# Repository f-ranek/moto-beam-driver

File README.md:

# Cel projektu

Celem projektu było zbudowanie prostego urządzenia, które wyłączy światła mijania, gdy nie są potrzebne.
Dedykowane dla motocykla Suzuki V-Strom 650, roczniki od 2017 wzwyż.

## Od strony użytkownika

Zacznijmy od tego, że podchodzę do motocykla, włączam stacyjkę. Normalnie światła już świecą, ale po co. Póki co mam odcięty zapłon na _kill-switch_, a bieg na luzie. Włączam _kill-switch_, odpalam moto, ale ja przecież jeszcze nigdzie nie jadę - kask trzeba ubrać, wsiąść, stopkę złożyć. I gdy już to wszystko jest zrobione, włączam bieg (magia, ta dam), światła się zapalają, a ja odjeżdżam. Niekoniecznie w stronę słońca, bo czasem razi, ale na pewno gdzieś daleko.

Dojeżdżając do skrzyżowania, wrzucam luz, ale wtedy światła już nie gasną. No chyba, że dojechałem do przejazdu kolejowego, i wiem, że chwilę postoję. Gaszę wtedy silnik, a po chwili światła automatycznie gasną. Zapalą się znów, gdy będzie włączony silnik i bieg.
A gdyby mi po drodze przez przypadek zgasł silnik, to światła zgasną również na czas kręcenia rozrusznikiem.

Dodatkowo, mam do dyspozycji przycisk, który zmienia stan świateł na przeciwne (włączone-wyłączone). Przykładowo, gdy chcę sobie poświecić. Albo na czas jazdy w _offie_ wyłączyć światła.

Funkcjonalność, której niestety nie zweryfikowałem w praktyce to utrzymywanie napięcia na żarówce na poziomie około 13,2 V napięcia skutecznego pomimo wahań napięcia w instalacji motocykla. Celem tego zabiegu jest przedłużenie żywotniści żarówki świateł mijania. Niestety, jak napisałem, z braku czasu nie sprawdziłem realnego zasięgu świateł przy obniżonym napięciu zasilania vs pełne napięcie z alternatora. Niemniej jednak obecnie zbudowany prototyp został wyposażony w czujnik zmierzchowy, który można włączyć w obwód przez aktualizację oprogramowania, i w przypadku wykrycia jazdy po zmierzchu, zasilić żarówkę pełną mocą. 

## Dioda

Dioda generalnie odzwierciedla stan świateł, tzn. powinna być włączona, gdy światła są włączone, oraz wyłączona, gdy są wyłączone.
Dodatkowo, po włączeniu stacyjki, świeci się przez trzy sekundy, nawet jeżeli światła są wyłączone.

Jeżeli dioda miga krótkimi, pojedynczymi „mrugnięciami”, bądź w podobny sposób gaśnie, to znaczy, że żarówka albo bezpiecznik są przepalone.

Po zgaszeniu silnika, ale zanim światła zgasną, jest jeszcze 5-cio sekundowy okres, w trakcie którego dioda świeci przez 0,8 sek, a następnie gaśnie na 0,2 sek.

Natomiast stan, gdy żarówka właśnie się zapala jest sygnalizowany świeceniem przez pół sekundy, i podobnie kolejne pół gaśnie. 

## Przycisk

Przycisk generalnie zmienia stan układu na przeciwny. Od tej reguły jest jeden wyjątek - przyciśnięcie go, gdy światła mają za chwilę zgasnąć (po zgaszeniu silnika) powoduje, że pozostaną włączone. Dodatkowo, przytrzymanie przycisku na dłużej niż sekundę zawsze gasi światła.

Powyższy diagram wydaje się być przerażająco skomplikowany, ale tak naprawdę realizuje logikę pozwalającą przełączać i automatycznie gasić światła.

Po załączeniu stacyjki aplikacja jest w stanie początkowym - 0.
Naciskając przycisk przy zgaszonym silniku wymuszamy włączenie i pozostawienie świateł włączonych - stany 6 i 7.
Naciskając przycisk przy włączonym silniku zapalamy światła, jednocześnie pozwalając im zgasnąć, gdy silnik zostanie zgaszony - stany 2 i 3.
Przytrzymując przycisk wymuszamy zgaszenie świateł - stan 1.

W stanie 2 światła się rozjaśniają, by automatycznie przejść do stanu 3, w którym świecą, ale mogą zgasnąć (stan 5) po pewnym czasie od zgaszenia silnika (stan 4 - przejściowy).

Podobnie ze stanu 5 po odpaleniu silnika światła się zapalą - stany 2 i 3.

Stany 6 i 7 to wymuszone włączenie świateł - nie zgasną po zgaszeniu silnika, a tylko na czas kręcenia rozrusznikiem (stan 8).

## Diody diagnostyczne

Na płytce umieszczono dwie dodatkowe diody LED - czerwoną, która jest de facto odpowiednikiem sygnalizacji braku ciśnienia oleju w silniku, oraz zieloną, która kodem Morse'a odzwierciedla obecny stan aplikacji.

# Sprzęt

## Mikrokontroler

Projekt został zrealizowany w oparciu o ATTiny 84A, aczkolwiek powinien dać się zaadaptować na inne mikrokontrolery o podobnych możliwościach sprzętowych. W szczególności na rodzinę ATTiny x4A.

### FUSE bits

Do domyślnej konfiguracji mikrokontrolera zostały wprowadzone następujące zmiany:
* włączenie timera watchdog,
* ustawienie detekcji spadku napięcia zasilania na około 4,3 V. Poniżej tej wartości mikrokontroler jest zablokowany w stanie RESET,
* praca z wewnętrznym zegarem 8 MHz.

**hfuse** - `0xCC`
**lfuse** - `0xE2`

## Moduł mocy

Moduł mocy oparty jest o tranzystor Q5 MOSFET IRFZ44N. Pozwala on na sterowanie prądem do 49 A przy oporności załączonego tranzystora na poziomie 17,5 mΩ. Żarówka pobiera mniej niż 5 A, i w takim stanie na tranzystorze jest tracone do 0,5 W mocy.

Sterowanie tranzystora Q5 jest zrealizowane za pomocą wzmacniacza w konfiguracji _totem pole_ Q2 i Q3 i adaptera poziomu TTL do 12V Q1. Ładowanie bramki odbywa się dodatkowo przez rezystor R16 10 kΩ. Zabieg ten ma na celu wydłużenie czasu przełączania tranzystora Q5, co powoduje zmniejszenie skoków prądu w instalacji, a tym samym generowanych przepięć i zakłóceń.

Jak wykazały testy, mimo pracy tranzystora Q5 przez pewną część czasu w obszarze liniowym, straty mocy na w/w tranzystorze są na tyle niewielkie, że nie wymaga on dodatkowego chłodzenia.

Na płytce zostało też wyprowadzone złącze J6. Domyślnie zwarte są nóżki 4 i 5. Ich rozwarcie powoduje, że tranzystor Q5 będzie zawsze w stanie nasycenia (żarówka włączona). Zwarcie nóżek 5 i 6 zwiera bramkę do masy, tym samym rozłączając tranzystor i gasząc żarówkę.

## Interfejsy z systemami motocykla

### Kabelkologia

Moduł mocy został wpięty w obwód żarówki świateł mijania za pomocą złącza o nr 11155 od strony motocykla, oraz 11156/12634 w kierunku żarówki. Dzięki takiemu rozwiązaniu awarię można wyeliminować rozpinając (wypinając) moduł z instalacji motocykla, i łącząc żarówkę po staremu - na krótko. Drugim sposobem eliminacji awarii jest rozłączenie nóżek 4 i 5 w złączu J6. Co prawda w takim przypadku nadal na ścieżce pozostaje tranzystor mocy Q5, ale jest to również rozwiązanie łatwiejsze i szybsze do przeprowadzenia. 

**UWAGI:** 

Ja zakupiłem takie złącza po okazyjnej cenie na pewnym dalekowschodnim portalu aukcyjnym. Jakość wykonanie wydaje się nie urągać europejskim standardom. Natomiast kupując te złącza należy zwrócić uwagę, aby kupić nie tylko obudowę (ang. *housing*), ale także PINy oraz uszczelnienia.

Od strony motocykla w złączu świateł mamy zasilanie 12 V po bezpieczniku świateł mijania - przewód w kolorze czarnym z niebieskim paskiem (B/Bl) - łączymy go z J5 układu, i jednocześnie przekazujemy dalej - na żarówkę. Przewód w kolorze czarnym z białym paskiem (B/W) to standardowo masa, i tę masę łączymy z J1 układu. Natomiast J10 wyprowadzamy na żarówkę.

Pomocny może być poniższy schemat:

**UWAGI:** 

1. Przed połączeniem czegokolwiek należy upewnić się, że na właściwych PINach motocykla mamy właściwe przewody, czyli masę oraz zasilanie w odpowiednim miejscu. Tutaj po prostu włączamy zapłon i sprawdzamy, czy napięcie 12 V jest w tym miejscu, w którym chcemy. 
Montując wtyczkę niestety łatwo o błąd i zamianę pinów lewego z prawym, a taka zamiana spowoduje, że układ nie będzie nam działał.
2. Przekazanie mocy na żarówkę należy wykonać przewodami o przekroju co najmniej 0,75 mm². Odnogę zasilania (J5) można już puścić cieńszym przewodem.
3. Lutując przewody mocy w układzie najlepiej przylutować je bezpośrednio do nóżek tranzystora, uważając przy tym, aby go nie przegrzać.

Połączenie J2 - dodatkowe zasilanie, jest opcjonalne, ale bez niego układ nam nie wykryje przepalenia bezpiecznika świateł mijania. Ja podłączyłem się do przewodu w kolorze białym z zielonym paskiem (W/G) - pojawia się tam napięcie po przekręceniu kluczyka, zabezpieczone bezpiecznikiem SIGNAL.

Połączenie J4 - dodatkowa masa. Dzięki temu można bezpiecznie rozłączyć wiązki prowadzące do świateł.

Połączenie J8 - wykrywanie braku ciśnienia oleju. Przewód zielony z żółtym paskiem (G/Y) - w momencie braku ciśnienia oleju jest zwierany do masy motocykla.

Połączenie J9 - wykrywanie biegu neutralnego. Przewód niebieski z czarnym paskiem (Bl/B) - w momencie wrzucenia „luzu” jest zwierany do masy motocykla.

Ja się wlutowałem w wiązkę w okolicach czachy motocykla.

Przy okazji przewody:
* czarnym z białym paskiem (B/W) to standardowo masa,
* czerwony z białym paskiem (R/W) to zasilanie dostępne nawet po wyjęciu kluczyka. Zabezpieczone bezpiecznikiem FUEL.

**UWAGI**

Przed przylutowaniem czegokolwiek najpierw sprawdź, czy to na pewno dobry przewód, i czy „zachowuje się” zgodnie z oczekiwaniami.

Wszystkie testy prowadź w takie sposób, że:
1. odłączasz ECM (dwie wtyczki) oraz zegary (jedna wtyczka) - jak coś spieprzysz, to najwyżej wyleci bezpiecznik,
2. minus miernika łączysz z masą motocykla, plus z punktem, który chcesz sprawdzić,
3. znajdź cieniutki, ale bardzo cieniutki stalowy drucik (ja mam taki ze sprężynki), i wsuwaj go do gniazda, np. po odpięciu zegarów,
4. odsuwając gumową osłonę wtyczki zegarów można sprawdzić kolory izolacji przewodów,
5. jeżeli sprawdzasz napięcie w obwodzie, sprawdź również, czy po przekręceniu kluczyka znika (bądź nie), oraz czy po wyjęciu odpowiedniego bezpiecznika znika.

# Programowanie

Ja korzystam po taniości z płytki Arduino połączonej z mikrokontrolerem, oraz _skeczu_ ArduinoISP dostępnego w ArduinoIDE.
Programowanie mikrokontrolera odbywa się przez `avrdude`, i np. żeby wejść w tryb interaktywny, należy wydać polecenie: `avrdude -v -p attiny84 -c arduino -P COM6 -b 19200 -t`, gdzie `COM6` oznacza nr portu, pod którym zarejestrowała się płytka Arduino podpięta do komputera.

Programowanie _fuse bit_ można wykonać wydając polecenie (w trybie interaktywnym `avrdude`):  
`write lfuse 0 0xE2`
`write hfuse 0 0xCC`  

# Oprogramowanie

Prawdopodobnie będziesz potrzebował(a) Microchip Studio, albo przynajmniej `avr-gcc`.

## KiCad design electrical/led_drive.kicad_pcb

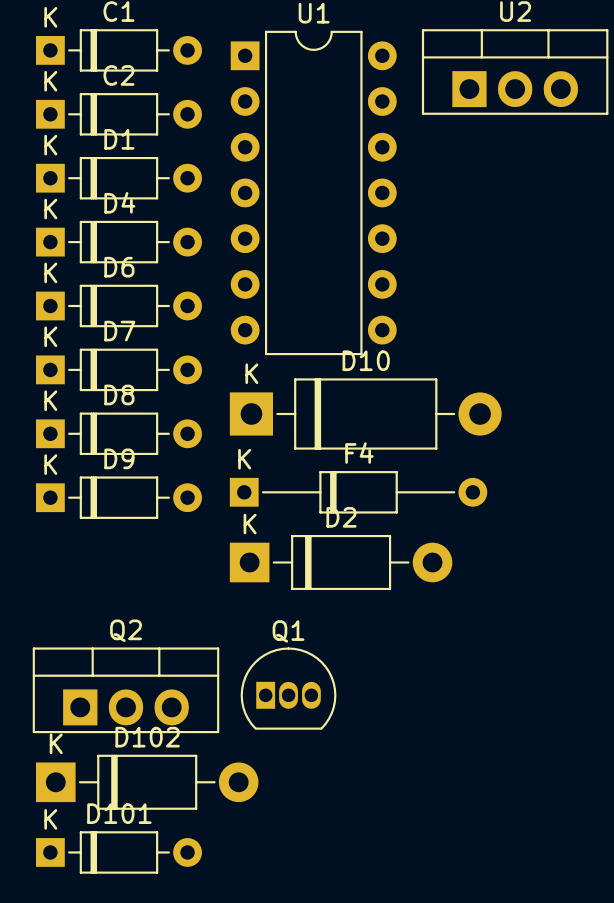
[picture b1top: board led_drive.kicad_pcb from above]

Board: 2 copper layers, 17 parts (0 on the bottom side), 7 nets, no tracks yet.

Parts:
C1, C2: 100n; D_DO-35_SOD27_P7.62mm_Horizontal
D1, D101: BZX55C 5.1V; D_DO-35_SOD27_P7.62mm_Horizontal
D2, D102: 1N4001; D_DO-41_SOD81_P10.16mm_Horizontal
D4, D6, D7, D8, D9: 1N4148; D_DO-35_SOD27_P7.62mm_Horizontal
D10: P6KE20CA; D_DO-15_P12.70mm_Horizontal
F4: LP60-075 0.75A; D_DO-35_SOD27_P12.70mm_Horizontal
Q1: BC547; TO-92_Inline
Q2: IRF5305; TO-220-3_Vertical
U1: ATtiny84A-PU; DIP-14_W7.62mm
U2: LM7905; TO-220-3_Vertical

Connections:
+5V: C2.1, D6.1 (K), D8.1 (K), U1.1 (VCC), U2.3 (VO)
GND: C1.2, C2.2, D1.1 (A), D7.2 (A), D9.2 (A), D101.1 (A), Q1.3 (E), Q2.2 (D), U1.14 (GND), U2.1 (GND)
unnamed: D4.2 (A), U1.12 (PA1)
unnamed: D6.2 (A), D7.1 (K), U1.2 (XTAL1/PB0)
unnamed: D8.2 (A), D9.1 (K), U1.3 (XTAL2/PB1)
POWER: D2.1 (K), D102.1 (K), F4.1
VDC: C1.1, F4.2, U2.2 (VI)

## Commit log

2023-02-13 Initial 3ms application code
2023-03-05 Poprawki
2023-03-05 Initial code for PWM
2023-03-05 Jakieś bzdury
2023-03-05 Zmiana nazwy projektu
2023-03-05 Dobra, coś to może i nawet robi
2023-03-06 Added PWM initial support
2023-03-07 Added license and readme
2023-03-26 Something (not) important
2023-03-26 Added first electrical diagram
2023-03-26 Added electrical diagram
2023-03-26 Fixed ERC warninigs
2023-03-27 Fixes in power module
2023-03-27 Added power module with MOSFET-N
2023-03-27 Appication development
2023-03-28 Application logic implementation
2023-03-28 Project cleanup
2023-03-28 Fixes for ADC reading and processing
2023-03-31 Updated according to recent changes
2023-03-31 Some code changes ;)
2023-04-01 Some project structore cleanup
2023-04-01 Trying to do some optimizations
2023-04-01 Fixed problem with button not working in initial state
2023-04-02 There's something wrong with this code, or device
2023-04-02 Looks like it is working as expected
2023-04-02 Moved initial button reading to main()
2023-04-02 Added some docs
2023-04-02 Conditional support for LED ADC
2023-04-02 Fixed a problem when power-on caused beam to be turned on
2023-04-02 Replaced bit values with _BV macro
2023-04-02 Trying to make it work at 4 MHz - failed
2023-04-02 So the proper prescaler and it works again, but we have too much LED blinking
2023-04-02 It looks random. We need to disable LED for longer to be able to read ADC results in any 'realiable' way
2023-04-03 Lepiej nie będzie
2023-04-03 Lepiej nie ruszać, bo lepiej nie będzie
2023-04-18 Some code refactoring
2023-04-18 Schematics export to PNGs
2023-04-18 Added more readme
2023-04-18 More readme
2023-04-19 Electrical diagram refactor
2023-04-27 What a terrible mistake - fixed BEAM IN/OUT
2024-03-04 electrical module draft
2024-03-04 code draft
2024-03-05 Work in progress
2024-03-05 Name refactor
2024-03-10 ADC decoding and smoothing
2024-03-10 Na razie lepiej nie będzie - trzeba wrócić, bo miga głównie na ostatnim bicie
2024-03-11 single shot ADC without disabling ADC at all???
2024-03-11 ADC work in progress
2024-03-12 Will it work?
2024-03-14 ADC finally working
2024-03-16 Ok, działa dość stabilnie
2024-03-16 Działa stabilnie, ale długo się zbiera
2024-03-16 OK, wygląda na to, że działa
2024-03-22 KiCad 8
2024-03-22 App workflow scratch
2024-03-22 Refactoring + workflow impl
2024-03-22 Działa, ale nie tak miało...
2024-03-22 New attempt to handle app state
2024-03-22 code cleanup and refactoring
2024-03-23 Dodanie informacji post-build o zajętości pamięci
2024-03-23 Jakoś to działa
2024-03-23 Add app states drawing
2024-03-23 Kosmetyka workflow - zobaczymy, co z tego będzie
2024-03-23 Szkic - Morse debug out
2024-03-23 App states fixes, Morse code longer delays
2024-03-23 Morse code refactor
2024-03-23 Aktualizacja KiCad i schematu - LED do debugowania
2024-04-04 8 MHz, more stable SPI
2024-04-05 Optimization of SPI code
2024-04-05 More debug, listing FUSES after build
2024-04-14 Względenie działa
2024-04-16 Twilight ADC
2024-04-17 Nowe podejście do sterowania żarówką
2024-04-18 Cache size of only 1
2024-04-18 Change brightening target calculation
2024-04-18 Detect app loop, some state transition fixes
2024-04-18 Include version info in build app
2024-04-20 Optimize version info generation
2024-04-20 Poprawki po testach
2024-05-20 Dodanie opisu projektu
